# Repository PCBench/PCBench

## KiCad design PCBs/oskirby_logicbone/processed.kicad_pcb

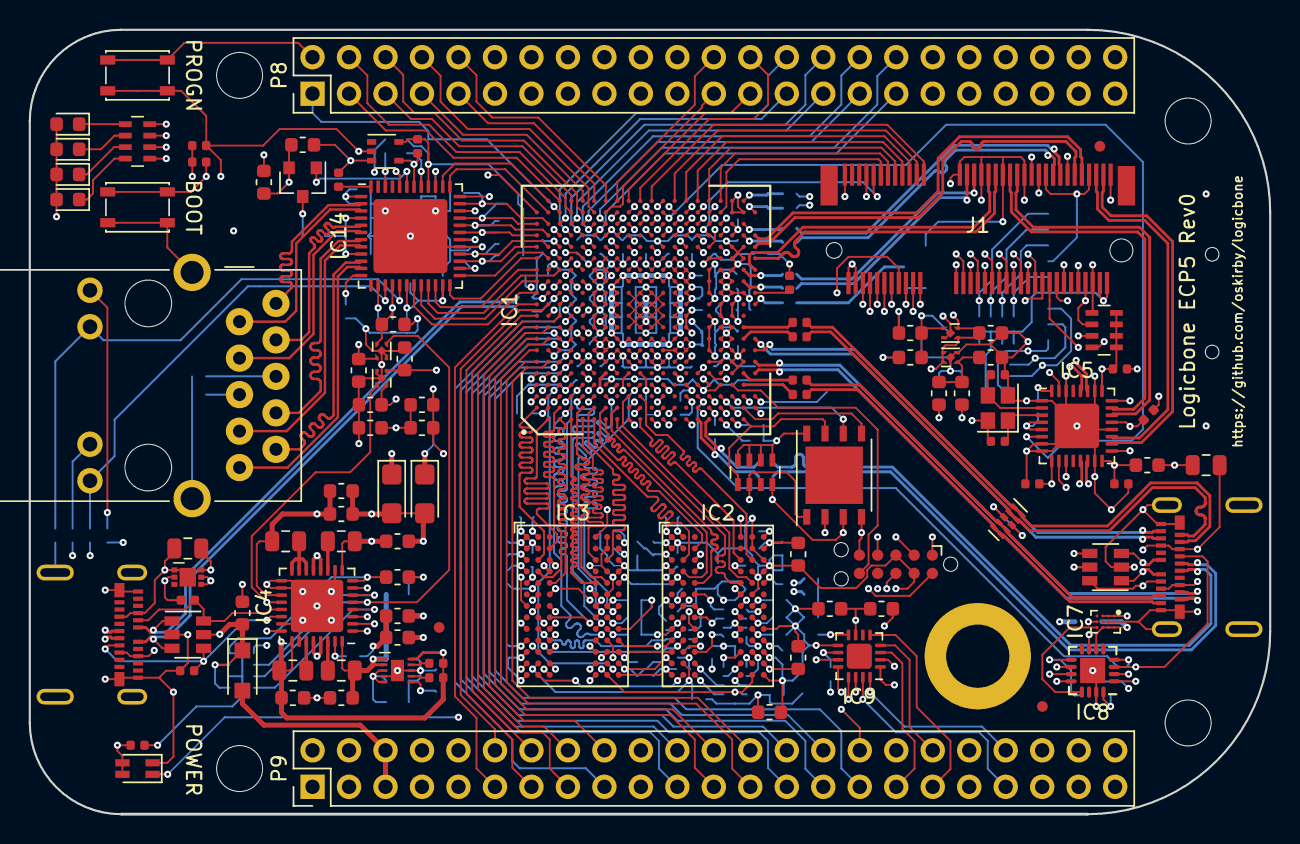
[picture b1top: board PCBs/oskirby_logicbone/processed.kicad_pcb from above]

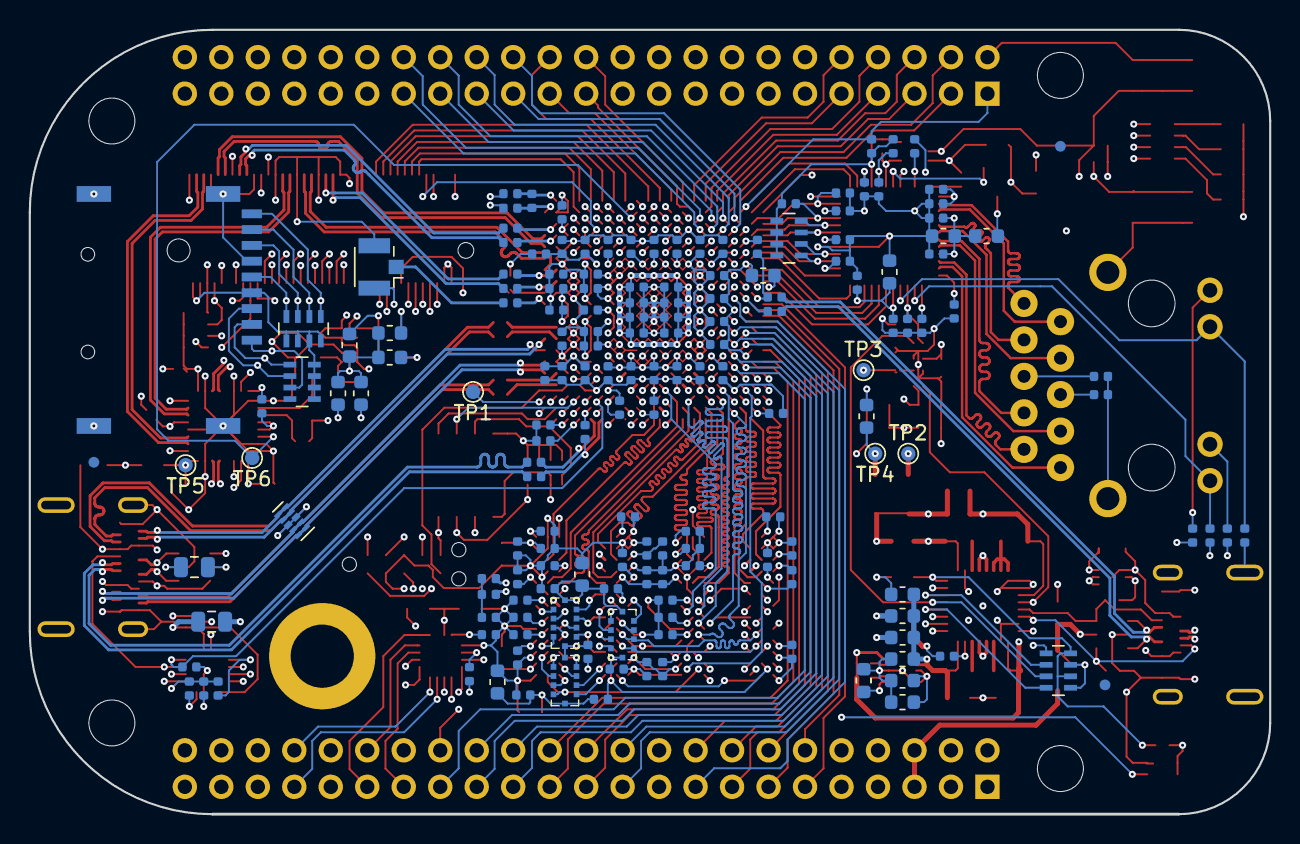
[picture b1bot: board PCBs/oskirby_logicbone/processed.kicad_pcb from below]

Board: 8 copper layers, 86.4 x 54.6 mm, 275 parts (169 on the bottom side), 313 nets.

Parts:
C101, C102, C103, C105, C106, C107, C110, C111, C112, C113, C114, C115, C116, C118, C120, C121, C122, C123, C124, C200, C201, C210, C211, C220, C221, C230, C231, C251, C257, C260, C261, C264, C265, C266, C280, C300, C301, C302, C309, C310, C311, C316, C317, C318, C319, C401, C402, C403, C411, C412, C413, C421, C422, C423, C431, C432, C433, C451, C452, C454, C455, C456, C461, C462, C463, C464, C465, C467, C469, C500, C501, C502, C503, C512, C522, C532, C542: 100nF; C_0402_1005Metric
C104, C117, C150, C151, C152, C153, C154, C155, C156, C157, C158, C159, C160, C161, C162, C163, C164, C165, C166, C167, C168, C169, C170, C250, C255, C303, C304, C308, C315, C400, C410, C420, C430, C440, C441, C442, C443, C445, C460, C533, C543: 10uF; C_0603_1608Metric
C108, C109: 12pF; C_0402_1005Metric
C119, C125, C126, C127: 4.7uF/35V; C_0805_2012Metric
C198, C199: 47uF; CP_EIA-3216-10_Kemet-I
C252, C253, C258, C259, C305, C306, C307, C312, C313, C314, C404, C405, C406, C414, C415, C424, C425, C426, C434, C435, C504, C505, C506, C507, C510, C511, C520, C521, C530, C531, C540, C541: 10nF; C_0402_1005Metric
D1: LED_RED_GREEN; LED_0805_DUAL
D2, D3, D4, D5: LED_ALT; LED_0603_1608Metric
D6: SS24FL; D_SOD-123F
D7, D8: D5V0F4U6SO; SOT-23-6
D9, D10: TPD4E02B04; USON-10_2.5x1.0mm_P0.5mm
FB1, FB2, FB3, FB4, FB5, FB7, FB8, FB9: MPZ1608S600; L_0603_1608Metric
FID1, FID2, FID3, FID4, FID5, FID6: Fiducial; Fiducial_0.75mm_Mask1.5mm
H1, H2, H3, H4: MountingHole; MountingHole_3.2mm_M3
H5: 9774025360; wurth-9774025360
IC1: ECP5UM-CABGA381; caBGA-381_20x20_17.0x17.0mm
IC2, IC3: DDR3-TFBGA78; FBGA-78_7.5x11mm_Layout2x3x13_P0.8mm
IC4: MXL7704; QFN-32-1EP_5x5mm_P0.5mm_EP3.65x3.65mm
IC5: PI6CG18401; QFN-32-1EP_5x5mm_P0.5mm_EP3.1x3.1mm
IC6: NCP349; DFN6_1.6x2mm
IC7: FPF2595; WLCSP-12_3x4_1.3x1.8mm
IC8: FUSB307; UQFN-16-1EP_3x3mm_P0.5mm_EP1.75x1.75mm
IC9: TLA2518; WQFN-16-1EP_3x3mm_P0.5mm_EP1.75x1.75mm
IC10: W25Q128; DFN-8-1EP_6x5mm_P1.27mm_EP4x4mm
IC12: 74LVC1G07; SOT-353_SC-70-5
IC13: TPS51206; WSON-10EP-2x2mm
IC14: KSZ9031RNXCC; QFN-48-1EP_7x7mm_P0.5mm_EP5.15x5.15mm
IC17, IC18: NCP110AMX110; UDFN-4-1EP_1x1mm_P0.65mm_EP0.48x0.48mm
IC19, IC20: NCP115AMX250; UDFN-4-1EP_1x1mm_P0.65mm_EP0.48x0.48mm
J1: NGFF-KEY-E; TE-2199230-4
J2, J5: USB_C_Receptacle; Molex-1054500101
J3: ARJM11xx-502; ARJM11B1_502
J4: TC2050-IDC-NL; Tag-Connect_TC2050-IDC-NL_2x05_P1.27mm_Vertical
J6: Micro_SD_MEM2075; MEM2075
J7: u.FL; U.FL_Hirose_U.FL-R-SMT-1_Vertical
L1: 2.2uH; L_0805_2012Metric
L2, L4: 0.47uH; L_0805_2012Metric
L3: 1uH; L_0805_2012Metric
P8, P9: BB_2x23; PinHeader_2x23_P2.54mm_Vertical
Q1: Q_PMOS_GSD; SOT-23
R1, R2, R6, R37: 33; R_0402_1005Metric
R3, R4, R10, R27, R28: 240; R_0402_1005Metric
R5, R39: 100; R_0402_1005Metric
R7: 12.1k; R_0402_1005Metric
R8, R13, R19, R20, R21, R22, R23, R24, R25, R29, R30, R31, R35: 10k; R_0402_1005Metric
R11, R12, R18, R32: 5.1k; R_0402_1005Metric
R14, R15, R16, R38: 47; R_0402_1005Metric
R17, R26: 1.5k; R_0402_1005Metric
R33: 750; R_0402_1005Metric
R34, R36: 1.2k; R_0402_1005Metric
RN1, RN2, RN3: 47; EXBD-1206
RN4, RN5, RN6, RN7, RN8, RN11: 10k; R_Array_Concave_4x0603
RN9: 470; R_Array_Concave_4x0603
SW1, SW2: SW_SPST; SW_SPST_PTS810
TP1: DONE; TestPoint_Pad_D1.0mm
TP2: VCORE; TestPoint_Pad_D1.0mm
TP3: VCCAUX; TestPoint_Pad_D1.0mm
TP4: VDDR; TestPoint_Pad_D1.0mm
TP5: VCC1V8; TestPoint_Pad_D1.0mm
TP6: 25MREF; TestPoint_Pad_D1.0mm
Y1: 25MHz; Crystal_SMD_2520-4Pin_2.5x2.0mm

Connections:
+3V3: C170.1, IC4.1, IC4.8, R10.2, R19.1, R29.1, RN5.6, RN5.8
/DDR3 Power/VDDR_CORE: C400.1, C401.1, C402.1, C403.1, C404.1, C405.1, C406.1, C420.1, C421.1, C422.1, C423.1, C424.1, C425.1, C426.1, FB9.2, IC2.A2, IC2.A9, IC2.D7, IC2.G2, IC2.G8, IC2.K1, IC2.K9, IC2.M1, IC2.M9, IC3.A2, IC3.A9, IC3.D7, IC3.G2, IC3.G8, IC3.K1, IC3.K9, IC3.M1, IC3.M9
/DDR3 Power/VDDR_IO: C410.1, C411.1, C412.1, C413.1, C414.1, C415.1, C430.1, C431.1, C432.1, C433.1, C434.1, C435.1, FB8.2, IC2.B9, IC2.C1, IC2.E2, IC2.E9, IC3.B9, IC3.C1, IC3.E2, IC3.E9
/Ethernet/25M_REFCLK: C102.1, IC1.M19, IC5.6, TP6.1
/Ethernet/ETH_1V2: C308.1, C309.1, C310.1, C311.1, C312.1, C313.1, C314.1, FB7.2, IC14.14, IC14.18, IC14.23, IC14.26, IC14.30, IC14.39, Q1.3
/Ethernet/ETH_AVDDL: C315.1, C316.1, C317.1, FB7.1, IC14.4, IC14.9, IC14.44
/Ethernet/ETH_LDO: IC14.43, Q1.1
/Ethernet/ETH_LED_L: IC14.15, J3.L4, R24.2
/Ethernet/ETH_LED_R: IC14.17, J3.L2, R25.2
/Ethernet/ETH_REFCLK: IC1.A19, IC14.41, R21.2, R22.2
/Ethernet/ETH_RXCLK: IC1.B18, IC14.35, R23.2
/Ethernet/ETH_RXCTL: IC1.A18, IC14.33, R20.2
/Ethernet/ETH_RXD0: IC1.B17, IC14.32, RN11.4
/Ethernet/ETH_RXD1: IC1.A17, IC14.31, RN11.3
/Ethernet/ETH_RXD2: IC1.B16, IC14.28, RN11.2
/Ethernet/ETH_RXD3: IC1.A16, IC14.27, RN11.1
/Ethernet/ETH_TRXD1N: IC14.3, J3.2
/Ethernet/ETH_TRXD1P: IC14.2, J3.1
/Ethernet/ETH_TRXD2N: IC14.6, J3.4
/Ethernet/ETH_TRXD2P: IC14.5, J3.3
/Ethernet/ETH_TRXD3N: IC14.8, J3.8
/Ethernet/ETH_TRXD3P: IC14.7, J3.7
/Ethernet/ETH_TRXD4N: IC14.11, J3.10
/Ethernet/ETH_TRXD4P: IC14.10, J3.9
/Ethernet/ETH_TXCLK: IC1.A15, IC14.24
/Ethernet/ETH_TXCTL: IC1.B15, IC14.25
/Ethernet/ETH_TXD0: IC1.A12, IC14.19
/Ethernet/ETH_TXD1: IC1.A13, IC14.20
/Ethernet/ETH_TXD2: IC1.C14, IC14.21
/Ethernet/ETH_TXD3: IC1.A14, IC14.22
/Ethernet/FPGA_USB+: D7.1, J2.A6, J2.B6, R1.1
/Ethernet/FPGA_USB-: D7.3, J2.A7, J2.B7, R2.1
/Ethernet/FPGA_USB_PULL: IC1.C16, R26.2
/Ethernet/LED_USER1: IC1.D16, J1.6, RN9.8
/Ethernet/LED_USER2: IC1.C15, J1.16, RN9.7
/Ethernet/LED_USER3: IC1.C13, RN9.6
/Ethernet/LED_USER4: IC1.B13, RN9.5
/Ethernet/MDIO_CLK: IC1.D12, IC14.36
/Ethernet/MDIO_DATA: IC1.B19, IC14.37
/Ethernet/MMC_CLK: IC1.E11, J6.5, RN6.4
/Ethernet/MMC_CMD: IC1.D15, J6.3, RN8.6
/Ethernet/MMC_DAT0: IC1.D13, J6.7, RN6.3
/Ethernet/MMC_DAT1: IC1.E13, J6.8, RN6.2
/Ethernet/MMC_DAT2: IC1.E15, J6.1, RN8.7
/Ethernet/MMC_DAT3: IC1.E14, J6.2, RN8.5
/Ethernet/MMC_DET: IC1.D14, J6.9, RN6.1
/Ethernet/~ETH_INT: IC1.B20, IC14.38
/Ethernet/~ETH_RESET: IC1.C17, IC12.4, IC14.42, R13.2
/Ethernet/~SYS_RESET: IC1.W3, IC12.2, J4.10, P9.10, R19.2, SW2.1
/Exp Headers/ADC_MISO: IC1.E8, IC9.12
/Exp Headers/ADC_MOSI: IC1.D10, IC9.14
/Exp Headers/ADC_SCLK: IC1.E9, IC9.13
/Exp Headers/CAPE_5V: D6.2, P9.5, P9.6
/Exp Headers/P8_LVDS1n: IC1.D19, P8.4
/Exp Headers/P8_LVDS1p: IC1.C20, P8.3
/Exp Headers/P8_LVDS2n: IC1.E19, P8.6
/Exp Headers/P8_LVDS2p: IC1.D20, P8.5
/Exp Headers/P8_LVDS3n: IC1.F19, P8.8
/Exp Headers/P8_LVDS3p: IC1.E20, P8.7
/Exp Headers/P8_LVDS4n: IC1.G20, P8.10
/Exp Headers/P8_LVDS4p: IC1.F20, P8.9
/Exp Headers/P8_LVDS5n: IC1.H20, P8.24
/Exp Headers/P8_LVDS5p: IC1.G19, P8.23
/Exp Headers/P8_LVDS6n: IC1.K20, P8.26
/Exp Headers/P8_LVDS6p: IC1.J20, P8.25
/Exp Headers/P8_LVDS7n: IC1.D17, P8.28
/Exp Headers/P8_LVDS7p: IC1.C18, P8.27
/Exp Headers/P8_LVDS8n: IC1.E17, P8.30
/Exp Headers/P8_LVDS8p: IC1.D18, P8.29
/Exp Headers/P8_LVDS9n: IC1.F18, P8.32
/Exp Headers/P8_LVDS9p: IC1.E18, P8.31
/Exp Headers/P8_LVDS10n: IC1.G18, P8.34
/Exp Headers/P8_LVDS10p: IC1.F17, P8.33
/Exp Headers/P8_LVDS11n: IC1.F16, P8.36
/Exp Headers/P8_LVDS11p: IC1.E16, P8.35
/Exp Headers/P8_LVDS12n: IC1.H16, P8.38
/Exp Headers/P8_LVDS12p: IC1.G16, P8.37
/Exp Headers/P8_LVDS13n: IC1.J16, P8.40
/Exp Headers/P8_LVDS13p: IC1.J17, P8.39
/Exp Headers/P8_LVDS14n: IC1.H17, P8.42
/Exp Headers/P8_LVDS14p: IC1.H18, P8.41
/Exp Headers/P8_LVDS15n: IC1.K19, P8.44
/Exp Headers/P8_LVDS15p: IC1.J19, P8.43
/Exp Headers/P8_LVDS16n: IC1.K18, P8.46
/Exp Headers/P8_LVDS16p: IC1.J18, P8.45
/Exp Headers/P9_AIN0: IC9.15, P9.39
/Exp Headers/P9_AIN1: IC9.16, P9.40
/Exp Headers/P9_AIN2: IC9.1, P9.37
/Exp Headers/P9_AIN3: IC9.2, P9.38
/Exp Headers/P9_AIN4: IC9.3, P9.33
/Exp Headers/P9_AIN5: IC9.4, P9.36
/Exp Headers/P9_AIN6: IC9.5, P9.35
/Exp Headers/P9_CLKOUT: IC1.B10, P9.41
/Exp Headers/P9_GPIO11: IC1.A11, P9.11
/Exp Headers/P9_GPIO12: IC1.B11, P9.12
/Exp Headers/P9_GPIO13: IC1.A10, P9.13
/Exp Headers/P9_GPIO14: IC1.C10, P9.14
/Exp Headers/P9_GPIO15: IC1.A9, P9.15
/Exp Headers/P9_GPIO16: IC1.B9, P9.16
/Exp Headers/P9_GPIO17: IC1.C11, P9.17
/Exp Headers/P9_GPIO18: IC1.A8, P9.18
/Exp Headers/P9_GPIO21: IC1.D9, P9.21
/Exp Headers/P9_GPIO22: IC1.C8, P9.22
/Exp Headers/P9_GPIO23: IC1.B8, P9.23
/Exp Headers/P9_GPIO24: IC1.A7, P9.24
/Exp Headers/P9_GPIO25: IC1.A6, P9.25
/Exp Headers/P9_GPIO26: IC1.B6, P9.26
/Exp Headers/P9_GPIO27: IC1.D8, P9.27
/Exp Headers/P9_GPIO42: IC1.E10, P9.42
/Exp Headers/P9_SPI_D0: IC1.D7, P9.29
/Exp Headers/P9_SPI_D1: IC1.C6, P9.30
/Exp Headers/P9_SPI_SCLK: IC1.D6, P9.31
/Exp Headers/PWR_BUTTON: IC1.U2, P9.9, R29.2, SW1.1
/Exp Headers/SCL: IC1.U1, IC4.3, IC5.10, IC8.12, J1.60, P9.19, R18.2
/Exp Headers/SDA: IC1.V1, IC4.2, IC5.11, IC8.11, J1.58, P9.20, R32.1
/Exp Headers/~ADC_CSEL: IC1.E6, IC9.11
/Exp Headers/~P9_SPI_CSEL: IC1.C7, P9.28
/FPGA Memory/DDR3_A0: IC1.D5, IC2.K3, IC3.K3, RN3.3
/FPGA Memory/DDR3_A1: IC1.F4, IC2.L7, IC3.L7, RN2.2
/FPGA Memory/DDR3_A2: IC1.B3, IC2.L3, IC3.L3, RN1.9
/FPGA Memory/DDR3_A3: IC1.F3, IC2.K2, IC3.K2, RN3.9
/FPGA Memory/DDR3_A4: IC1.E5, IC2.L8, IC3.L8, RN2.8
/FPGA Memory/DDR3_A5: IC1.C3, IC2.L2, IC3.L2, RN3.2
/FPGA Memory/DDR3_A6: IC1.C4, IC2.M8, IC3.M8, RN2.9
/FPGA Memory/DDR3_A7: IC1.A5, IC2.M2, IC3.M2, R14.2
/FPGA Memory/DDR3_A8: IC1.A3, IC2.N8, IC3.N8, RN2.6
/FPGA Memory/DDR3_A9: IC1.B5, IC2.M3, IC3.M3, RN2.4
/FPGA Memory/DDR3_A10: IC1.G3, IC2.H7, IC3.H7, RN1.4
/FPGA Memory/DDR3_A11: IC1.F5, IC2.M7, IC3.M7, RN2.3
/FPGA Memory/DDR3_A12: IC1.D2, IC2.K7, IC3.K7, RN1.3
/FPGA Memory/DDR3_A13: IC1.A4, IC2.N3, IC3.N3, RN2.5
/FPGA Memory/DDR3_A14: IC1.D3, IC2.N7, IC3.N7, RN2.7
/FPGA Memory/DDR3_A15: IC1.E3, IC2.J7, IC3.J7, RN1.8
/FPGA Memory/DDR3_BA0: IC1.B4, IC2.J2, IC3.J2, RN3.8
/FPGA Memory/DDR3_BA1: IC1.H5, IC2.K8, IC3.K8, RN1.2
/FPGA Memory/DDR3_BA2: IC1.N2, IC2.J3, IC3.J3, RN3.5
/FPGA Memory/DDR3_CK+: IC1.M4, IC2.F7, IC3.F7, R15.2
/FPGA Memory/DDR3_CK-: IC1.N5, IC2.G7, IC3.G7, R16.1
/FPGA Memory/DDR3_CKE: IC1.K4, IC2.G9, IC3.G9, RN1.5
/FPGA Memory/DDR3_DM0: IC1.L4, IC2.A7
/FPGA Memory/DDR3_DM1: IC1.J5, IC3.A7
/FPGA Memory/DDR3_DQ0: IC1.G2, IC2.B3
/FPGA Memory/DDR3_DQ1: IC1.K1, IC2.C7
/FPGA Memory/DDR3_DQ2: IC1.F1, IC2.C2
/FPGA Memory/DDR3_DQ3: IC1.K3, IC2.C8
/FPGA Memory/DDR3_DQ4: IC1.H2, IC2.E3
/FPGA Memory/DDR3_DQ5: IC1.J3, IC2.E8
/FPGA Memory/DDR3_DQ6: IC1.G1, IC2.D2
/FPGA Memory/DDR3_DQ7: IC1.H1, IC2.E7
/FPGA Memory/DDR3_DQ8: IC1.B1, IC3.B3
/FPGA Memory/DDR3_DQ9: IC1.E1, IC3.C7
/FPGA Memory/DDR3_DQ10: IC1.A2, IC3.C2
/FPGA Memory/DDR3_DQ11: IC1.F2, IC3.C8
/FPGA Memory/DDR3_DQ12: IC1.C1, IC3.E3
/FPGA Memory/DDR3_DQ13: IC1.E2, IC3.E8
/FPGA Memory/DDR3_DQ14: IC1.C2, IC3.D2
/FPGA Memory/DDR3_DQ15: IC1.D1, IC3.E7
/FPGA Memory/DDR3_DQS0+: IC1.K2, IC2.C3
/FPGA Memory/DDR3_DQS0-: IC1.J1, IC2.D3
/FPGA Memory/DDR3_DQS1+: IC1.H4, IC3.C3
/FPGA Memory/DDR3_DQS1-: IC1.G5, IC3.D3
/FPGA Memory/DDR3_ODT: IC1.C5, IC2.G1, IC3.G1, RN3.6
/FPGA Memory/DDR3_VREF: C460.1, C461.1, C462.2, C463.1, C464.1, C465.1, C467.1, IC1.B2, IC1.K5, IC2.E1, IC2.J8, IC3.E1, IC3.J8, IC13.6
/FPGA Memory/~DDR3_CAS: IC1.M1, IC2.G3, IC3.G3, RN3.4
/FPGA Memory/~DDR3_CS: IC1.M3, IC2.H2, IC3.H2, RN3.7
/FPGA Memory/~DDR3_RAS: IC1.L1, IC2.F3, IC3.F3, RN1.6
/FPGA Memory/~DDR3_RST: IC1.P1, IC2.N2, IC3.N2
/FPGA Memory/~DDR3_WE: IC1.E4, IC2.H3, IC3.H3, RN1.7
/FPGA Power/PGOOD: D1.2, D1.4, IC4.20, IC20.3, R10.1, RN5.1
/FPGA Power/PMIC_ENABLE: IC4.6, RN5.2
/FPGA Power/PMIC_PG1: IC4.5, IC19.3, RN5.3
/FPGA Power/PMIC_SEQ: IC4.4, RN5.4
/FPGA Power/USB_UFP_CC1: D7.6, IC4.21, J2.A5, R12.2
/FPGA Power/USB_UFP_CC2: D7.4, IC4.22, J2.B5, R11.1
/FPGA Power/VCCA0: C530.1, C531.1, C532.1, C533.1, FB2.2, IC1.T6, IC1.U6
/FPGA Power/VCCA1: C540.1, C541.1, C542.1, C543.1, FB3.2, IC1.T15, IC1.U15
/FPGA SERDES/FPGA_REFCLK+: IC1.P3, IC5.13, R39.2
/FPGA SERDES/FPGA_REFCLK-: IC1.P4, IC5.14, R39.1
/FPGA SERDES/M2_COEX1: IC1.P18, J1.44
/FPGA SERDES/M2_COEX2: IC1.N18, J1.46
/FPGA SERDES/M2_COEX3: IC1.N17, J1.48
/FPGA SERDES/M2_CTS: IC1.R18, J1.34
/FPGA SERDES/M2_PCM_CLK: IC1.U16, J1.8
/FPGA SERDES/M2_PCM_IN: IC1.P16, J1.12
/FPGA SERDES/M2_PCM_OUT: IC1.T16, J1.14
/FPGA SERDES/M2_PCM_SYNC: IC1.N16, J1.10
/FPGA SERDES/M2_RTS: IC1.U18, J1.36
/FPGA SERDES/M2_RXD: IC1.R17, J1.22
/FPGA SERDES/M2_SDIO_CLK: IC1.T17, J1.9
/FPGA SERDES/M2_SDIO_CMD: IC1.U19, J1.11
/FPGA SERDES/M2_SDIO_DATA0: IC1.U20, J1.13
/FPGA SERDES/M2_SDIO_DATA1: IC1.T20, J1.15
/FPGA SERDES/M2_SDIO_DATA2: IC1.R20, J1.17
/FPGA SERDES/M2_SDIO_DATA3: IC1.P20, J1.19
/FPGA SERDES/M2_SUSCLK: IC1.L16, J1.50
/FPGA SERDES/M2_TXD: IC1.U17, J1.32
/FPGA SERDES/M2_VEND0: IC1.P19, J1.42
/FPGA SERDES/M2_VEND1: IC1.T19, J1.40
/FPGA SERDES/M2_VEND2: IC1.P17, J1.38
/FPGA SERDES/PCIE_REFCLK0+: IC5.23, J1.47
/FPGA SERDES/PCIE_REFCLK0-: IC5.22, J1.49
/FPGA SERDES/PCIE_REFCLK1+: IC5.19, J1.71
/FPGA SERDES/PCIE_REFCLK1-: IC5.18, J1.73
/FPGA SERDES/PCIE_RX0+: IC1.Y14, J1.41
/FPGA SERDES/PCIE_RX0-: IC1.Y15, J1.43
/FPGA SERDES/PCIE_RX1+: IC1.Y16, J1.65
/FPGA SERDES/PCIE_RX1-: IC1.Y17, J1.67
/FPGA SERDES/PCIE_TX0+: C115.2, J1.35
/FPGA SERDES/PCIE_TX0-: C114.2, J1.37
/FPGA SERDES/PCIE_TX1+: C113.2, J1.59
/FPGA SERDES/PCIE_TX1-: C112.2, J1.61
/FPGA SERDES/SERDES_REFCLK+: C111.2, IC5.28
/FPGA SERDES/SERDES_REFCLK-: C110.2, IC5.27
/FPGA SERDES/VCCTRX1: C255.1, C257.1, C258.1, C259.1, FB5.1, IC1.T11, IC1.T12, IC1.T13, IC1.T14
/FPGA SERDES/~M2_ALERT: IC1.L19, J1.62
/FPGA SERDES/~M2_SDIO_RESET: IC1.L20, J1.23
/FPGA SERDES/~M2_SDIO_WAKE: IC1.N20, J1.21
/FPGA SERDES/~M2_UART_WAKE: IC1.T18, J1.20
/FPGA SERDES/~M2_WDIS1: IC1.L17, J1.56
/FPGA SERDES/~M2_WDIS2: IC1.M18, J1.54
/FPGA SERDES/~PCIE_CLKREQ0: IC5.24, J1.53, RN4.4
/FPGA SERDES/~PCIE_CLKREQ1: IC5.17, J1.68, RN4.2
/FPGA SERDES/~PCIE_RESET0: IC1.M17, J1.52
/FPGA SERDES/~PCIE_RESET1: IC1.N19, J1.66
/FPGA SERDES/~PCIE_WAKE0: IC1.L18, J1.55, RN4.3
/FPGA SERDES/~PCIE_WAKE1: IC1.M20, J1.70, RN4.1
/USB and Programming/DFP_SOURCE_EN: IC7.D3, IC8.13
/USB and Programming/EXT_REFCLK: C124.2, J7.1
/USB and Programming/FLASH_D2: IC1.Y2, IC10.3, RN7.4
/USB and Programming/FLASH_D3: IC1.W1, IC10.7, RN7.1
/USB and Programming/FLASH_MISO: IC1.V2, IC10.2
/USB and Programming/FLASH_MOSI: IC1.W2, IC10.5
/USB and Programming/FLASH_SCLK: IC1.U3, IC10.6
/USB and Programming/FPGA_DONE: IC1.Y3, TP1.1
/USB and Programming/FPGA_TCK: IC1.T5, J4.4
/USB and Programming/FPGA_TDI: IC1.R5, J4.8
/USB and Programming/FPGA_TDO: IC1.V4, J4.6
/USB and Programming/FPGA_TMS: IC1.U5, J4.2
/USB and Programming/FPGA_USB_DFP+: IC1.R1, R6.1, R17.2
/USB and Programming/FPGA_USB_DFP-: IC1.T1, R37.2
/USB and Programming/USBC_DFP+: D8.1, J5.A6, J5.B6, R6.2
/USB and Programming/USBC_DFP-: D8.3, J5.A7, J5.B7, R37.1
/USB and Programming/USBSS_RX1+: D10.1, D10.10, IC1.Y5, J5.B11
/USB and Programming/USBSS_RX1-: D10.2, D10.9, IC1.Y6, J5.B10
/USB and Programming/USBSS_RX2+: D10.5, D10.6, IC1.Y7, J5.A11
/USB and Programming/USBSS_RX2-: D10.4, D10.7, IC1.Y8, J5.A10
/USB and Programming/USBSS_TX1+: C103.2, D9.5, D9.6, J5.A2
/USB and Programming/USBSS_TX1-: C105.2, D9.4, D9.7, J5.A3
/USB and Programming/USBSS_TX2+: C106.2, D9.2, D9.9, J5.B2
/USB and Programming/USBSS_TX2-: C107.2, D9.1, D9.10, J5.B3
/USB and Programming/USB_DFP_CC1: D8.6, IC8.1, J5.A5
/USB and Programming/USB_DFP_CC2: D8.4, IC8.3, J5.B5
/USB and Programming/USB_DFP_PULL: IC1.T2, R17.1
/USB and Programming/USB_DFP_VBUS: C126.1, C127.1, IC7.A3, IC7.B3, IC7.C3, IC8.6, J5.A4, J5.A9, J5.B4, J5.B9
/USB and Programming/USB_ORIENT: IC1.R3, IC8.4, R35.2
/USB and Programming/VCCTRX0: C250.1, C251.1, C252.1, C253.1, FB4.1, IC1.T7, IC1.T8, IC1.T9, IC1.T10
/USB and Programming/~FLASH_CSEL: IC1.R2, IC10.1, RN7.2
/USB and Programming/~FPGA_INIT: D1.1, IC1.V3
/USB and Programming/~USB_INT: IC1.T3, IC8.10
GND: C101.2, C104.2, C108.2, C109.2, C116.2, C117.2, C118.2, C119.2, C120.2, C121.2, C122.2, C123.2, C125.2, C126.2, C127.2, C150.2, C151.2, C152.2, C153.2, C154.2, C155.2, C156.2, C157.2, C158.2, C159.2, C160.2, C161.2, C162.2, C163.2, C164.2, C165.2, C166.2, C167.2, C168.2, C169.2, C170.2, C198.2, C199.2, C200.2, C201.2, C210.2, C211.2, C220.2, C221.2, C230.2, C231.2, C250.2, C251.2, C252.2, C253.2, C255.2, C257.2, C258.2, C259.2, C260.2, C261.2, C264.2, C265.2, C266.2, C280.2, C300.2, C301.2, C302.2, C303.2, C304.2, C305.2, C306.2, C307.2, C308.2, C309.2, C310.2, C311.2, C312.2, C313.2, C314.2, C315.2, C316.2, C317.2, C318.2, C319.2, C400.2, C401.2, C402.2, C403.2, C404.2, C405.2, C406.2, C410.2, C411.2, C412.2, C413.2, C414.2, C415.2, C420.2, C421.2, C422.2, C423.2, C424.2, C425.2, C426.2, C430.2, C431.2, C432.2, C433.2, C434.2, C435.2, C440.2, C441.2, C442.2, C443.2, C445.2, C451.2, C452.2, C454.2, C455.2, C456.2, C460.2, C461.2, C462.1, C463.2, C464.2, C465.2, C467.2, C469.2, C500.2, C501.2, C502.2, C503.2, C504.2, C505.2, C506.2, C507.2, C510.2, C511.2, C512.2, C520.2, C521.2, C522.2, C530.2, C531.2, C532.2, C533.2, C540.2, C541.2, C542.2, C543.2, D1.3, D7.2, D8.2, D9.3, D9.8, D10.3, D10.8, H5.1, IC1.B7, IC1.B14, IC1.C19, IC1.D4, IC1.F7, IC1.F8, IC1.F13, IC1.F14, IC1.G4, IC1.G6, IC1.G7, IC1.G8, IC1.G9, IC1.G10, IC1.G11, IC1.G12, IC1.G13, IC1.G14, IC1.G15, IC1.G17, IC1.H19, IC1.J2, IC1.J7, IC1.J9, IC1.J10, IC1.J11, IC1.J12, IC1.J14, IC1.K6, IC1.K7, IC1.K9, IC1.K10, IC1.K11, IC1.K12, IC1.K14, IC1.K15, IC1.L9, IC1.L10, IC1.L11, IC1.L12, IC1.M2, IC1.M7, IC1.M9, IC1.M10, IC1.M11, IC1.M12, IC1.M14, IC1.M16, IC1.N6, IC1.N7, IC1.N14, IC1.N15, IC1.P7, IC1.P8, IC1.P11, IC1.P12, IC1.P13, IC1.P14, IC1.R4, IC1.R19, IC1.U4, IC1.U7, IC1.U8, IC1.U9, IC1.U10, IC1.U11, IC1.U12, IC1.U13, IC1.U14, IC1.V5, IC1.V6, IC1.V7, IC1.V8, IC1.V9, IC1.V12, IC1.V13, IC1.V14, IC1.V15, IC1.V16, IC1.V19, IC1.V20, IC1.W6, IC1.W7, IC1.W12, IC1.W15, IC1.W16, IC1.W19, IC2.A1, IC2.A8, IC2.B1, IC2.B2, IC2.B8, IC2.C9, IC2.D1, IC2.D8, IC2.D9, IC2.F2, IC2.F8, IC2.J1, IC2.J9, IC2.L1, IC2.L9, IC2.N1, IC2.N9, IC3.A1, IC3.A8, IC3.B1, IC3.B2, IC3.B8, IC3.C9, IC3.D1, IC3.D8, IC3.D9, IC3.F2, IC3.F8, IC3.J1, IC3.J9, IC3.L1, IC3.L9, IC3.N1, IC3.N9, IC4.10, IC4.17, IC4.18, IC4.23, IC4.26, IC4.33, IC5.1, IC5.7, IC5.8, IC5.15, IC5.20, IC5.26, IC5.30, IC5.33, IC6.2, IC6.6, IC7.A2, IC7.B2, IC7.C2, IC8.15, IC8.17, IC9.9, IC10.4, IC12.3, IC13.4, IC13.8, IC13.11, IC14.29, IC14.49, IC17.2, IC17.5, IC18.2, IC18.5, IC19.2, IC19.5, IC20.2, IC20.5, J1.1, J1.7, J1.18, J1.33, J1.39, J1.45, J1.51, J1.57, J1.63, J1.69, J1.75, J2.A1, J2.A12, J2.B1, J2.B12, J2.S1, J3.SH, J4.3, J4.5, J4.9, J5.A1, J5.A12, J5.B1, J5.B12, J5.S1, J6.6, J6.10, J7.2, P8.1, P8.2, P9.1, P9.2, P9.34, P9.43, P9.44, P9.45, P9.46, R3.2, R4.2, R7.1, R11.2, R12.1, R22.1, R23.1, R24.1, R25.1, R35.1, R36.1, R38.2, SW1.2, SW2.2, Y1.2, Y1.4
unnamed: C101.1, IC4.24, IC4.31
unnamed: C102.2, IC14.46
unnamed: C103.1, IC1.W4
unnamed: C105.1, IC1.W5
unnamed: C106.1, IC1.W8
unnamed: C107.1, IC1.W9
unnamed: C108.1, IC5.3, Y1.1
unnamed: C109.1, IC5.2, Y1.3
unnamed: C110.1, IC1.W20, R5.2
unnamed: C111.1, IC1.Y19, R5.1
unnamed: C112.1, IC1.W18
unnamed: C113.1, IC1.W17
unnamed: C114.1, IC1.W14
unnamed: C115.1, IC1.W13
unnamed: C116.1, IC9.8
unnamed: C117.1, FB1.1, IC9.7
unnamed: C119.1, IC6.1, IC6.7, J2.A4, J2.A9, J2.B4, J2.B9
unnamed: C124.1, IC1.Y11
unnamed: C318.1, J3.5
unnamed: C319.1, J3.6
unnamed: C469.1, R15.1, R16.2
unnamed: D2.1, RN9.1
unnamed: D3.1, RN9.2
unnamed: D4.1, RN9.3
unnamed: D5.1, RN9.4
unnamed: IC1.B12, R1.2, R26.1
unnamed: IC1.C12, R2.2
unnamed: IC1.Y12, R38.1
unnamed: IC2.H8, R3.1
unnamed: IC3.H8, R4.1
unnamed: IC4.11, L3.1
unnamed: IC4.14, IC4.15, IC4.16, L2.1
unnamed: IC4.27, L1.1
unnamed: IC4.30, L4.1
unnamed: IC5.32, R8.2
unnamed: IC7.D2, R33.2, R34.2, R36.2
unnamed: IC8.9, R33.1
unnamed: IC8.16, R34.1
unnamed: IC13.7, R31.1
unnamed: IC13.9, R30.1
unnamed: IC14.48, R7.2
unnamed: J3.L1, R27.2
unnamed: J3.L3, R28.2
VBUS: C104.1, C125.1, D6.1, D7.5, D8.5, IC4.7, IC4.12, IC4.13, IC4.28, IC4.29, IC6.4, IC6.5, IC7.A1, IC7.B1, IC7.C1, P9.7, P9.8, RN5.5, RN5.7
VCC1V8: C120.1, C121.1, C122.1, C123.1, C163.1, C164.1, C165.1, C230.1, C231.1, IC1.L14, IC1.L15, IC1.M15, IC4.9, IC5.4, IC5.5, IC5.9, IC5.16, IC5.21, IC5.25, IC5.31, IC17.3, IC17.4, IC18.3, IC18.4, L3.2, P9.32, R8.1, RN4.5, RN4.6, RN4.7, RN4.8, TP5.1
VCC3V3: C118.1, C160.1, C161.1, C162.1, C200.1, C201.1, C210.1, C211.1, C220.1, C221.1, C280.1, C300.1, C301.1, C302.1, C303.1, C304.1, C305.1, C306.1, C307.1, D2.2, D3.2, D4.2, D5.2, FB1.2, IC1.F9, IC1.F10, IC1.F11, IC1.F12, IC1.H14, IC1.H15, IC1.J15, IC1.P9, IC1.P10, IC1.T4, IC4.25, IC8.2, IC8.7, IC9.10, IC10.8, IC12.5, IC13.10, IC14.1, IC14.12, IC14.16, IC14.34, IC14.40, IC19.4, IC20.4, J1.2, J1.4, J1.72, J1.74, J4.1, J6.4, L1.2, P9.3, P9.4, Q1.2, R13.1, R18.1, R20.1, R21.1, R27.1, R28.1, R30.2, R31.2, R32.2, RN6.5, RN6.6, RN6.7, RN6.8, RN7.5, RN7.6, RN7.7, RN7.8, RN8.1, RN8.2, RN8.3, RN8.4, RN11.5, RN11.6, RN11.7, RN11.8
VCCAUX: C166.1, C510.1, C511.1, C512.1, IC1.F6, IC1.F15, IC1.P6, IC1.P15, IC20.1, TP3.1
VCCAUXTRX: C167.1, C520.1, C521.1, C522.1, IC1.V10, IC1.V11, IC1.V17, IC1.V18, IC19.1
VCCTRX: C168.1, FB4.2, FB5.2, IC17.1
VCCTRXA: C169.1, FB2.1, FB3.1, IC18.1
VCORE: C150.1, C151.1, C152.1, C153.1, C154.1, C155.1, C199.1, C500.1, C501.1, C502.1, C503.1, C504.1, C505.1, C506.1, C507.1, IC1.H8, IC1.H9, IC1.H10, IC1.H11, IC1.H12, IC1.H13, IC1.J8, IC1.J13, IC1.K8, IC1.K13, IC1.L8, IC1.L13, IC1.M8, IC1.M13, IC1.N8, IC1.N9, IC1.N10, IC1.N11, IC1.N12, IC1.N13, IC4.19, L2.2, TP2.1
VDDR: C156.1, C157.1, C158.1, C159.1, C198.1, C260.1, C261.1, C264.1, C265.1, C266.1, FB8.1, FB9.1, IC1.H6, IC1.H7, IC1.J6, IC1.L6, IC1.L7, IC1.M6, IC4.32, IC13.1, IC13.2, L4.2, TP4.1
VTT: C440.1, C441.1, C442.1, C443.1, C445.1, C451.1, C452.1, C454.1, C455.1, C456.1, IC13.3, IC13.5, R14.1, RN1.1, RN2.1, RN3.1

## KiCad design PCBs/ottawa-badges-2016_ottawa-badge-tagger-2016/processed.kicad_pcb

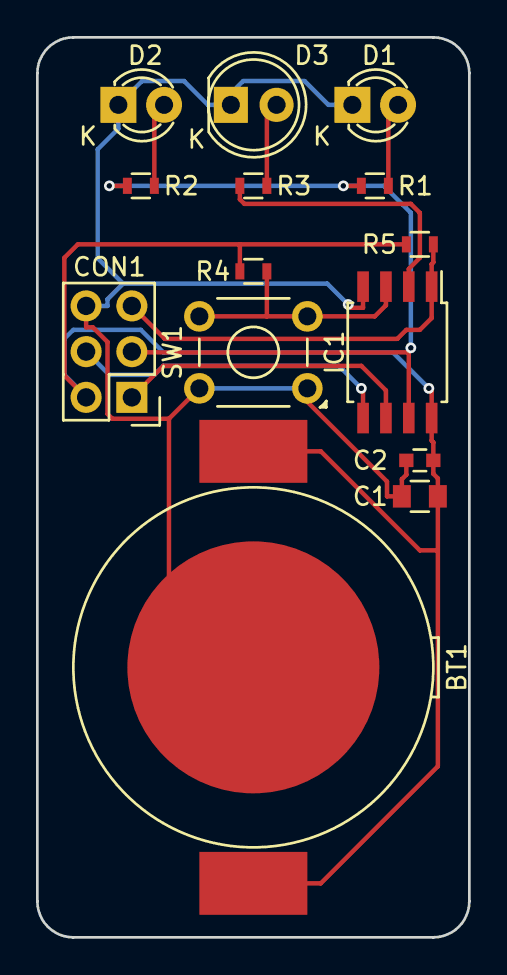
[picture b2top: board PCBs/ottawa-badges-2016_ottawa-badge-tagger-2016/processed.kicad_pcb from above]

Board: 2 copper layers, 24.0 x 50.0 mm, 14 parts (0 on the bottom side), 11 nets.

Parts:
BT1: Battery; CR2032-SHRAPNEL
C1: 1u; C_0805
C2: 100n; C_0603
CON1: AVR-ISP-6; Pin_Header_Straight_2x03
D1, D2: LED; LED-3MM
D3: LED; LED-5MM
IC1: ATTINY25-S; SOIJ-8_5.3x5.3mm_Pitch1.27mm
R1, R2, R3: 220; R_0603
R4, R5: 10K; R_0603
SW1: SW_PUSH; SW_TH_Tactile_Omron_B3F-10xx

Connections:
+3V3: BT1.1, C1.1, C2.1, CON1.2, IC1.8, R4.1, R5.1
/IROUT: IC1.2, R3.1
/MISO: CON1.1, IC1.6
/MOSI: CON1.4, IC1.5
/RESET: CON1.5, IC1.1, R5.2
/SCK/ACT: CON1.3, IC1.7, R1.1, R2.1
/TRIGGER: IC1.3, R4.2, SW1.2
GND: BT1.2, C1.2, C2.2, CON1.6, D1.1, D2.1, D3.1, IC1.4, SW1.1
unnamed: D1.2, R1.2
unnamed: D2.2, R2.2
unnamed: D3.2, R3.2

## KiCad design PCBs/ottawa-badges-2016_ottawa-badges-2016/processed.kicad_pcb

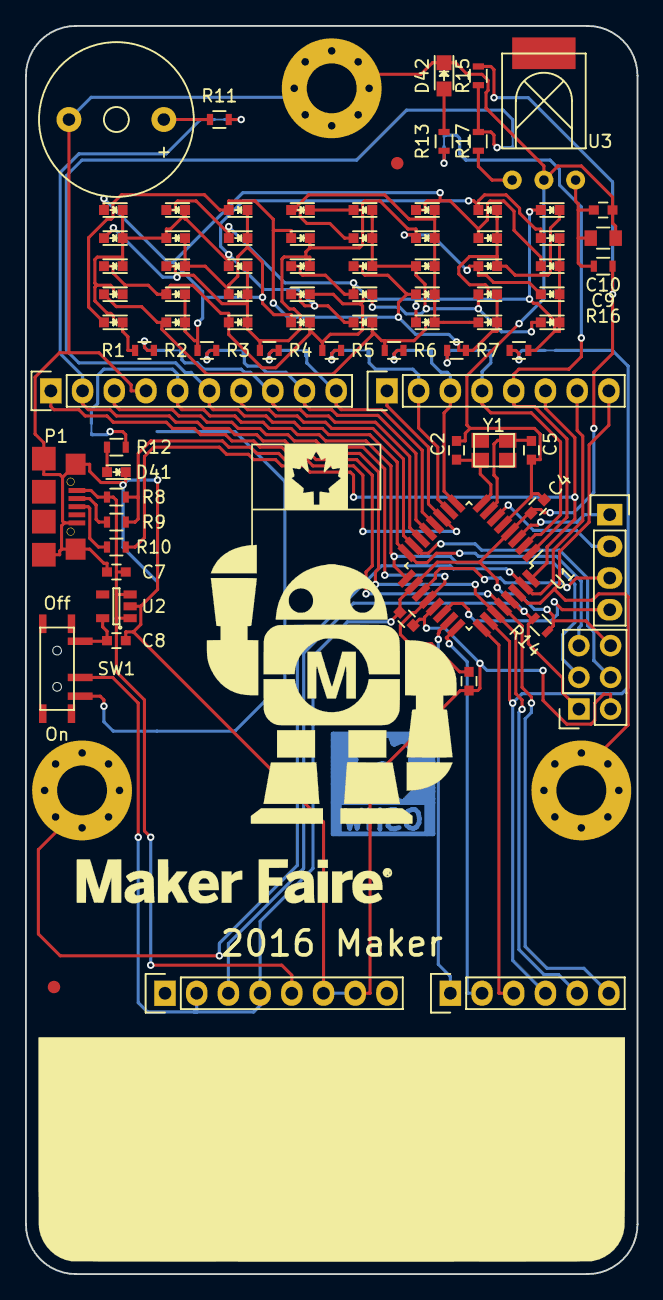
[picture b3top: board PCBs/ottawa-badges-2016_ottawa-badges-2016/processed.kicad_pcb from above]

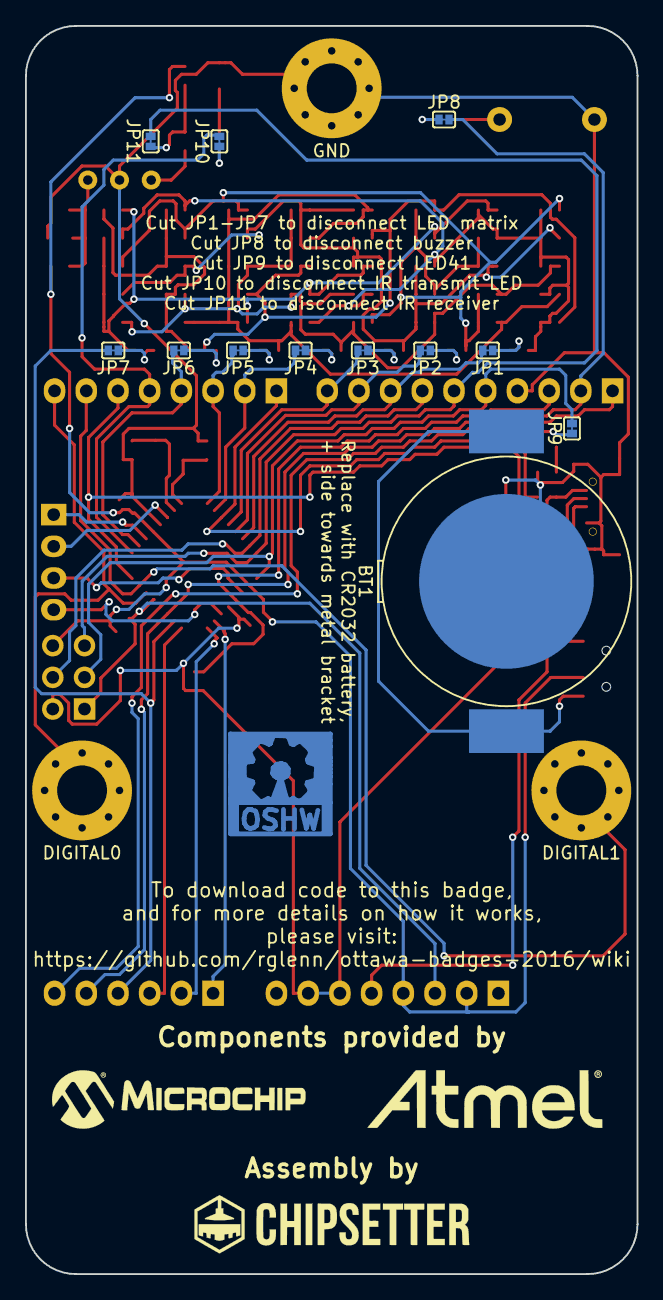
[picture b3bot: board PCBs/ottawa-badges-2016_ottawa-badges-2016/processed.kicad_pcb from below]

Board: 2 copper layers, 49.0 x 100.0 mm, 96 parts (12 on the bottom side), 58 nets.

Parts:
BT1: CR2032; CR2032-SHRAPNEL
C1, C4, C6, C10: 100n; C_0603
C2, C5: 18p; C_0603
C7, C8: 1u; C_0603
C9: 10u; C_0805
D1, D2, D3, D4, D5, D6, D7, D8, D9, D10, D11, D12, D13, D14, D15, D16, D17, D18, D19, D20, D21, D22, D23, D24, D25, D26, D27, D28, D29, D30, D31, D32, D33, D34, D35, D36, D37, D38, D39, D40, D41: Led_Small; LED_0603
D42: Led_Small; LED_0805
JP1, JP2, JP3, JP4, JP5, JP6, JP7, JP8, JP9, JP10, JP11: Jumper_NC_Small; SJ2
P1: USB_OTG; 10118192-0001LF
P2, P5: CONN_01X08; Socket_Strip_Straight_1x08
P3: CONN_01X06; Socket_Strip_Straight_1x06
P4: CONN_01X10; Socket_Strip_Straight_1x10
P6: CONN_02X03; Socket_Strip_Straight_2x03
P7, P8, P10: CONN_01X01; MountingHole_4mm_Pad_Via
P9: CONN_01X04; Socket_Strip_Straight_1x04
R1, R2, R3, R4, R5, R6, R7, R9, R10, R16: 56; R_0603
R8: 1.5K; R_0603
R11, R12, R13, R17: 1K; R_0603
R14, R15: 10K; R_0603
SP1: SPEAKER; Buzzer_12x9.5RM7.6
SW1: SWITCH_INV; MK-12C02
U1: ATMEGA328P-A; TQFP-32_7x7mm_Pitch0.8mm
U2: MIC5504-3.3YM5; SOT-23-5
U3: VS1838B; VS1838B-HORIZ
Y1: 12 MHz; crystal_FA238-TSX3225

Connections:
+3V3: C4.1, C6.1, P2.2, P2.4, P6.6, R14.2, R15.2, R16.2, SW1.2, U1.4, U1.18
+5V: C7.1, P1.1, P2.5, R8.1, U2.1, U2.3
/ANALOG0: P3.1, U1.23
/ANALOG1: P3.2, U1.24
/ANALOG2: P3.3, U1.25
/ANALOG3: JP7.1, P3.4, U1.26
/ANALOG4: JP8.1, P3.5, P4.2, U1.27
/ANALOG5: P3.6, P4.1, U1.28
/AREF: C1.1, P4.3, U1.20
/DIGITAL0: P5.8, P7.1, U1.30
/DIGITAL1: P5.7, P8.1, U1.31
/DIGITAL2: P5.6, R10.2, U1.32
/DIGITAL3: JP10.1, P5.5, U1.1
/DIGITAL4: JP6.1, P5.4, U1.2
/DIGITAL5: JP5.1, P5.3, U1.9
/DIGITAL6: JP4.1, P5.2, U1.10
/DIGITAL7: P5.1, R8.2, R9.2, U1.11
/DIGITAL8: JP3.1, P4.10, U1.12
/DIGITAL9: JP2.1, P4.9, U1.13
/DIGITAL10: JP1.1, P4.8, U1.14
/DIGITAL11: P4.7, P6.4, U1.15
/DIGITAL12: JP11.1, P4.6, P6.5, U1.16
/DIGITAL13: JP9.1, P4.5, P6.3, U1.17
/PE0: P9.1, U1.3
/PE1: P9.2, U1.6
/PE2: P9.3, U1.19
/PE3: P9.4, U1.22
/RESET: P2.3, P6.1, R14.1, U1.29
GND: BT1.2, C1.2, C2.2, C4.2, C5.2, C6.2, C7.2, C8.2, C9.2, C10.2, D41.1, D42.1, P1.5, P1.6, P2.6, P2.7, P4.4, P6.2, P10.1, SP1.2, U1.5, U1.21, U2.2, U3.2
unnamed: BT1.1, SW1.1
unnamed: C2.1, U1.8, Y1.1
unnamed: C5.1, U1.7, Y1.2
unnamed: C8.1, SW1.3, U2.5
unnamed: C9.1, C10.1, R16.1, U3.3
unnamed: D1.1, D2.1, D3.1, D4.1, D5.1, D6.1, D7.2, D13.2, D19.2, D25.2, D31.2, D37.2, R1.1
unnamed: D1.2, D7.1, D8.1, D9.1, D10.1, D11.1, D12.1, D14.2, D20.2, D26.2, D32.2, D38.2, R2.1
unnamed: D4.2, D10.2, D16.2, D22.2, D25.1, D26.1, D27.1, D28.1, D29.1, D30.1, D35.2, R5.1
unnamed: D5.2, D11.2, D17.2, D23.2, D29.2, D31.1, D32.1, D33.1, D34.1, D35.1, D36.1, R6.1
unnamed: D6.2, D12.2, D18.2, D24.2, D30.2, D36.2, D37.1, D38.1, D39.1, D40.1, R7.1
unnamed: D2.2, D8.2, D13.1, D14.1, D15.1, D16.1, D17.1, D18.1, D21.2, D27.2, D33.2, D39.2, R3.1
unnamed: D3.2, D9.2, D15.2, D19.1, D20.1, D21.1, D22.1, D23.1, D24.1, D28.2, D34.2, D40.2, R4.1
unnamed: D41.2, R12.1
unnamed: D42.2, R13.1
unnamed: JP1.2, R1.2
unnamed: JP2.2, R2.2
unnamed: JP3.2, R3.2
unnamed: JP4.2, R4.2
unnamed: JP5.2, R5.2
unnamed: JP6.2, R6.2
unnamed: JP7.2, R7.2
unnamed: JP8.2, R11.2
unnamed: JP9.2, R12.2
unnamed: JP10.2, R13.2
unnamed: JP11.2, R15.1, R17.2
unnamed: P1.2, R9.1
unnamed: P1.3, R10.1
unnamed: R11.1, SP1.1
unnamed: R17.1, U3.1

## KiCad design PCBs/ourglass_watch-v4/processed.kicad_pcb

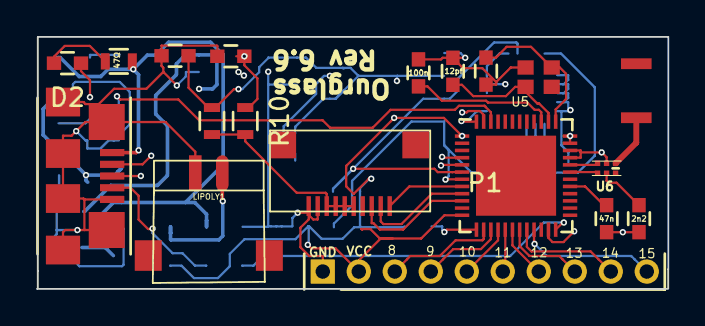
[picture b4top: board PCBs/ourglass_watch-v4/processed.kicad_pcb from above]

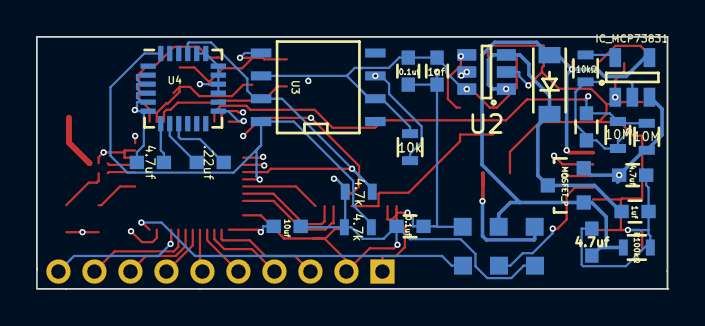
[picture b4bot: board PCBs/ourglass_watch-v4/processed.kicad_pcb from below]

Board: 4 copper layers, 35.1 x 14.0 mm, 43 parts (24 on the bottom side), 41 nets.

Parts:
ANT1: -; antenna
C1, C16, C17: 1uf; C_0603
C2, C3, C6: 4.7uf; C_0603
C4: 100n; C_0603
C5: .22uf; C_0603
C7: 10uf; C_0603
C8, C13: 0.1uf; C_0603
C9: 47n; C_0603
C10, C15: 12pf; C_0603
C11: 2n2; C_0603
C12: 1u; C_0603
C14: 1nf; C_0603
D1: DIODESCH; SOD-123
D2: LED; C_0603
J1: CONN_10; omron_XF2M-1015-1A-2
LIPOLY1: BATTERY; JST_2_pos
P1: Expansion Header; Pin_Header_Straight_1x10_Pitch2.00mm
P2: Test Points; test_points
Q1: MOSFET_P; SOT-23
R1: 47Ω; R_0603
R2: 10kΩ; R_0603
R3: R100kΩ; R_0603
R4: 10k; R_0603
R5, R6: 4.7k; R_0603
R7, R8: 10M; R_0603
R9, R10: 0; R_0603
U1: IC_MCP73831; SOT-23-5
U2: MIC5211; SOT-23-6
U3: DS3231; SOIC-8-N
U4: LSM9DS0; QFN-24-NO-CENTER4x4mm_Pitch0.5mm
U5: NRF51822; UQFN-48-1EP_6x6mm_Pitch0.4mm
U6: BALUN; BALUN-6
X1: 16mhz; SMD-Crystal
XL1: USB_MICRO_B; USB_Micro-B

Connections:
/5v_VCC: C17.1, R10.1, U2.4
/Accel_INT: U4.13, U5.48
/Bal1: U5.31, U6.4
/Bal2: U5.32, U6.3
/BatterySense: C12.1, R7.2, R8.1, U5.46
/ClockINT: R4.2, U3.3, U5.47
/Display_MOSI: J1.2, U5.9
/Display_SCK: J1.3, U5.10
/Display_SS: J1.1, U5.8
/EX8: P1.3, U5.14
/EX9: P1.4, U5.15
/EX10: P1.5, U5.16
/EX11: P1.6, U5.17
/EX12: P1.7, U5.18
/EX13: P1.8, U5.19
/EX14: P1.9, U5.20
/EX15: P1.10, U5.21
/EXTVCC: C2.1, D1.1, P2.5, Q1.1, R1.2, R3.1, U1.4, XL1.1
/RX: U5.5, XL1.3
/Regulator_In: C1.1, D1.2, Q1.3, U2.1, U2.3, U2.5
/Reset: P2.2, U5.23, XL1.4
/SCL: R5.1, U3.7, U4.21, U5.6
/SDA: R6.1, U3.8, U4.24, U5.7
/SWDCLK: P2.3, U5.24
/TX: U5.4, XL1.2
/VBAT: C3.1, LIPOLY1.2, P2.4, Q1.2, R7.1, U1.3
/VCC: C7.1, C8.1, C13.2, C14.2, C16.1, P1.2, P2.1, R4.1, R5.2, R6.2, R9.1, U2.6, U3.2, U3.6, U4.15, U4.16, U4.17, U4.18, U4.19, U4.20, U5.1, U5.12, U5.35, U5.36
/XC1: C10.1, U5.38, X1.3
/XC2: C15.1, U5.37, X1.1
GND: C1.2, C2.2, C3.2, C4.2, C6.2, C7.2, C8.2, C9.2, C10.2, C11.2, C12.2, C13.1, C14.1, C15.2, C16.2, C17.2, J1.9, J1.10, LIPOLY1.1, P1.1, P2.6, R2.2, R3.2, R8.2, U1.2, U2.2, U3.5, U4.2, U4.3, U4.4, U4.5, U4.6, U5.13, U5.33, U5.34, U6.2, X1.2, XL1.5
unnamed: ANT1.1, U6.1
unnamed: C4.1, U5.39
unnamed: C5.1, U4.9
unnamed: C5.2, U4.8
unnamed: C6.1, U4.7
unnamed: C9.1, U5.29
unnamed: C11.1, U6.5
unnamed: D2.1, U1.1
unnamed: D2.2, R1.1
unnamed: J1.5, J1.6, J1.7, J1.8, R9.2, R10.2
unnamed: R2.1, U1.5

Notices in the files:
PCBs/oskirby_logicbone/processed.kicad_pcb:
Licensed under CERN OHL v1.2
